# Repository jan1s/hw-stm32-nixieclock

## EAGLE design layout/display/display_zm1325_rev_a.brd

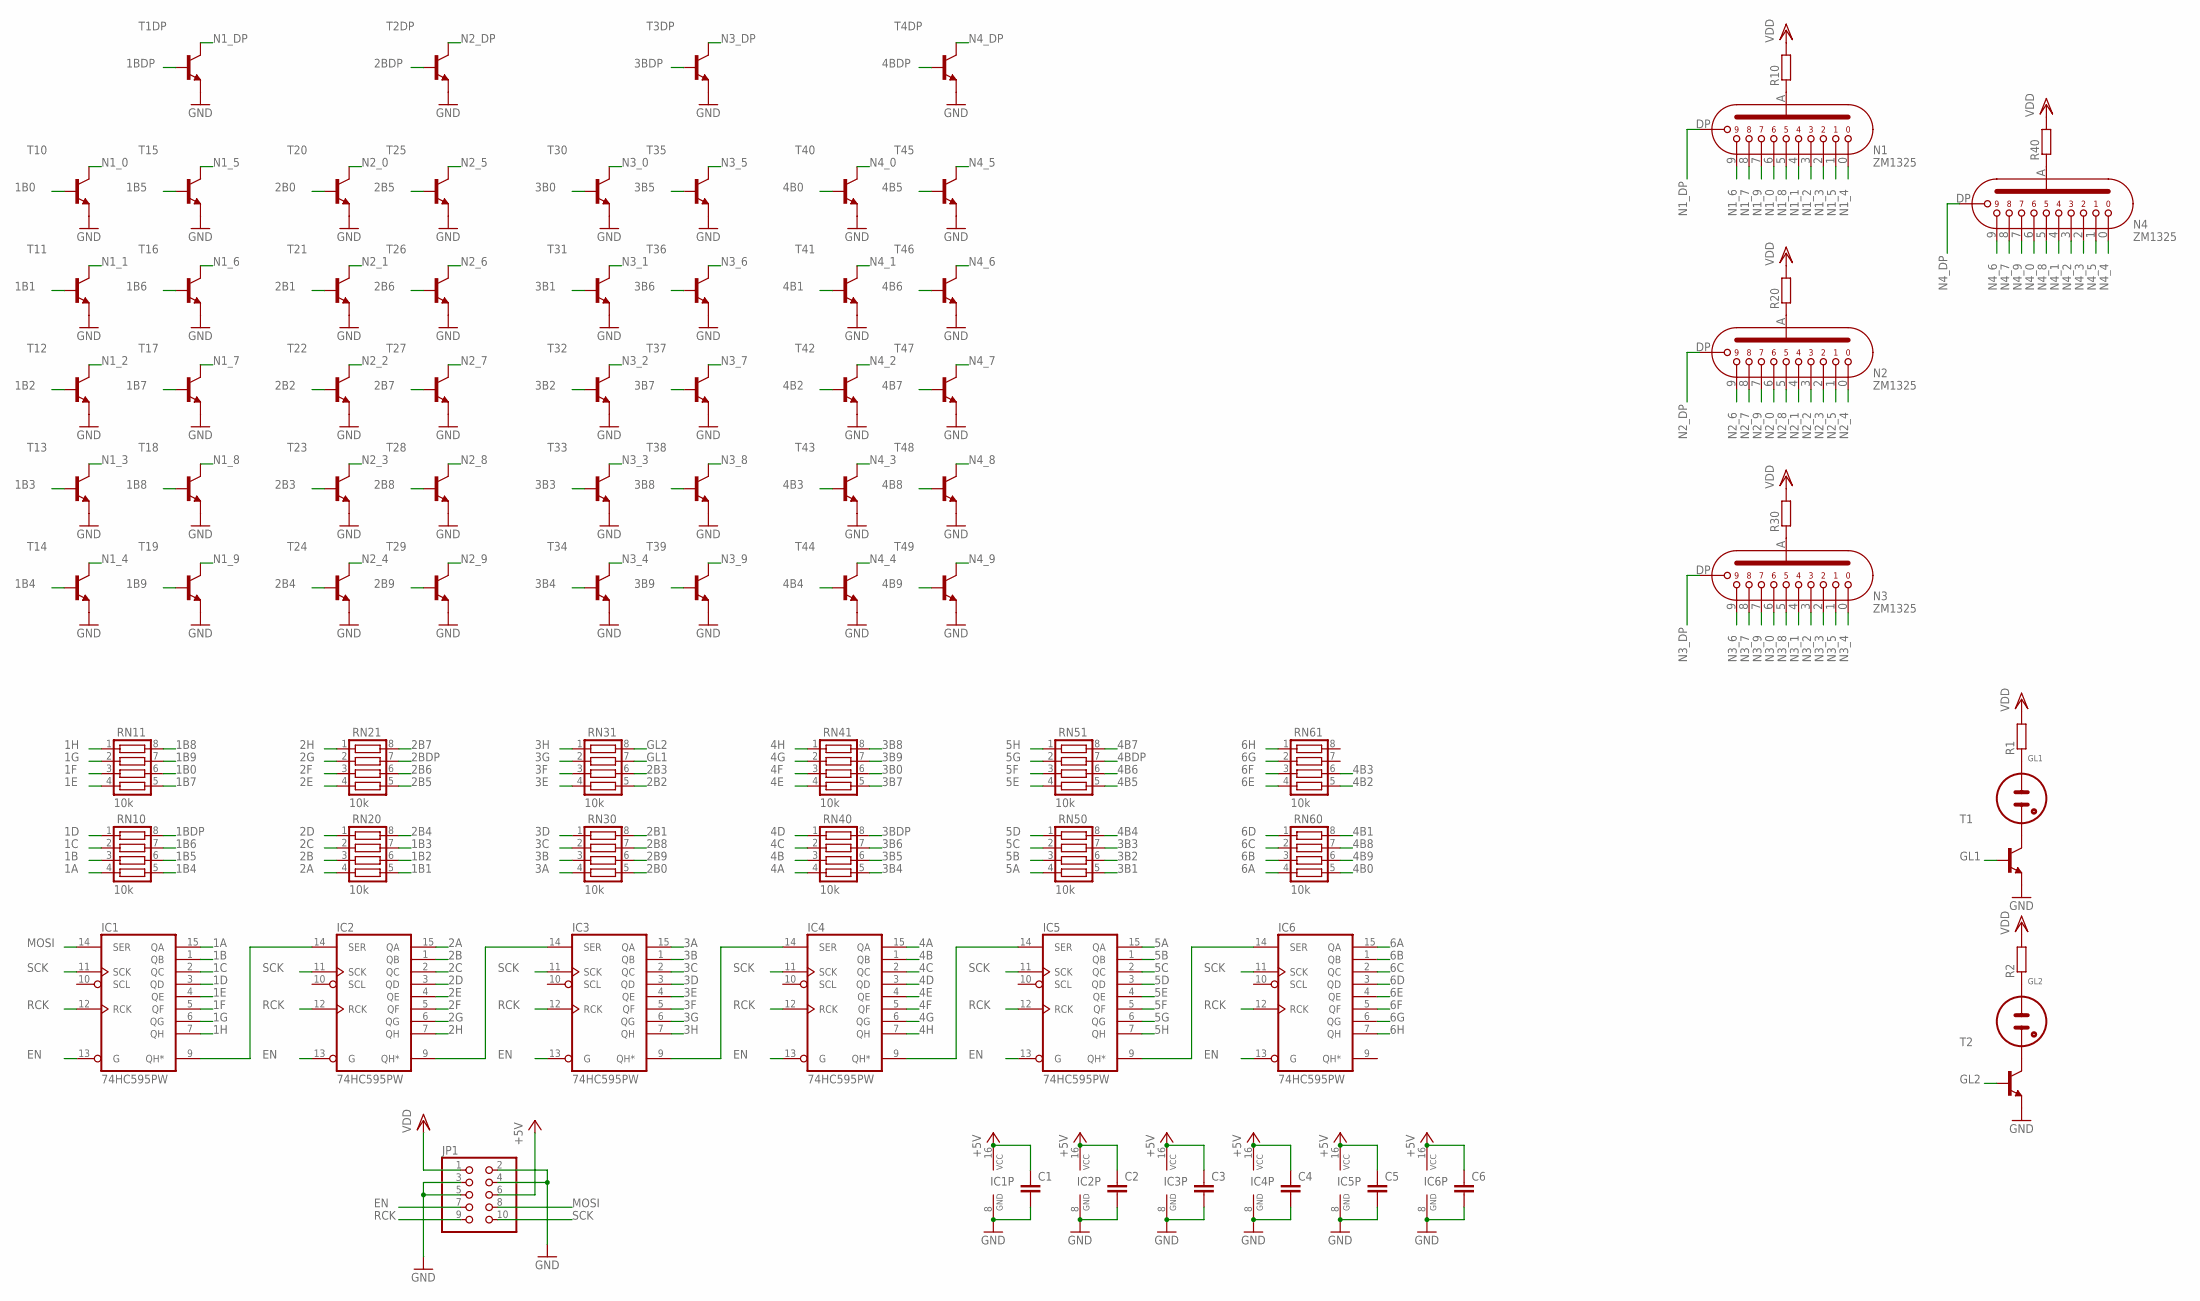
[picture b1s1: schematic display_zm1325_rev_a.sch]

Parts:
C1, C2, C3, C4, C5, C6: C-EUC0603; C0603
GL1, GL2: NE2-NEON-BULB-DRILL
IC1, IC2, IC3, IC4, IC5, IC6: 74HC595PW; TSSOP16
JP1: PINHD-2X5_2.54-SMD; 2X05SMD
N1, N2, N3, N4: ZM1325
R1, R2, R10, R20, R30, R40: R-EU_R0603; R0603
RN10, RN11, RN20, RN21, RN30, RN31, RN40, RN41, RN50, RN51, RN60, RN61: 10k; CTS742C083
T1, T1DP, T2, T2DP, T3DP, T4DP, T10, T11, T12, T13, T14, T15, T16, T17, T18, T19, T20, T21, T22, T23, T24, T25, T26, T27, T28, T29, T30, T31, T32, T33, T34, T35, T36, T37, T38, T39, T40, T41, T42, T43, T44, T45, T46, T47, T48, T49: SMBTA42; SOT23

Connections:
1A: IC1.15 (QA), RN10.4
1B: IC1.1 (QB), RN10.3
1B0: RN11.6, T10.1 (B)
1B1: RN20.5, T11.1 (B)
1B2: RN20.6, T12.1 (B)
1B3: RN20.7, T13.1 (B)
1B4: RN10.5, T14.1 (B)
1B5: RN10.6, T15.1 (B)
1B6: RN10.7, T16.1 (B)
1B7: RN11.5, T17.1 (B)
1B8: RN11.8, T18.1 (B)
1B9: RN11.7, T19.1 (B)
1BDP: RN10.8, T1DP.1 (B)
1C: IC1.2 (QC), RN10.2
1D: IC1.3 (QD), RN10.1
1E: IC1.4 (QE), RN11.4
1F: IC1.5 (QF), RN11.3
1G: IC1.6 (QG), RN11.2
1H: IC1.7 (QH), RN11.1
2A: IC2.15 (QA), RN20.4
2B: IC2.1 (QB), RN20.3
2B0: RN30.5, T20.1 (B)
2B1: RN30.8, T21.1 (B)
2B2: RN31.5, T22.1 (B)
2B3: RN31.6, T23.1 (B)
2B4: RN20.8, T24.1 (B)
2B5: RN21.5, T25.1 (B)
2B6: RN21.6, T26.1 (B)
2B7: RN21.8, T27.1 (B)
2B8: RN30.7, T28.1 (B)
2B9: RN30.6, T29.1 (B)
2BDP: RN21.7, T2DP.1 (B)
2C: IC2.2 (QC), RN20.2
2D: IC2.3 (QD), RN20.1
2E: IC2.4 (QE), RN21.4
2F: IC2.5 (QF), RN21.3
2G: IC2.6 (QG), RN21.2
2H: IC2.7 (QH), RN21.1
3A: IC3.15 (QA), RN30.4
3B: IC3.1 (QB), RN30.3
3B0: RN41.6, T30.1 (B)
3B1: RN50.5, T31.1 (B)
3B2: RN50.6, T32.1 (B)
3B3: RN50.7, T33.1 (B)
3B4: RN40.5, T34.1 (B)
3B5: RN40.6, T35.1 (B)
3B6: RN40.7, T36.1 (B)
3B7: RN41.5, T37.1 (B)
3B8: RN41.8, T38.1 (B)
3B9: RN41.7, T39.1 (B)
3BDP: RN40.8, T3DP.1 (B)
3C: IC3.2 (QC), RN30.2
3D: IC3.3 (QD), RN30.1
3E: IC3.4 (QE), RN31.4
3F: IC3.5 (QF), RN31.3
3G: IC3.6 (QG), RN31.2
3H: IC3.7 (QH), RN31.1
4A: IC4.15 (QA), RN40.4
4B: IC4.1 (QB), RN40.3
4B0: RN60.5, T40.1 (B)
4B1: RN60.8, T41.1 (B)
4B2: RN61.5, T42.1 (B)
4B3: RN61.6, T43.1 (B)
4B4: RN50.8, T44.1 (B)
4B5: RN51.5, T45.1 (B)
4B6: RN51.6, T46.1 (B)
4B7: RN51.8, T47.1 (B)
4B8: RN60.7, T48.1 (B)
4B9: RN60.6, T49.1 (B)
4BDP: RN51.7, T4DP.1 (B)
4C: IC4.2 (QC), RN40.2
4D: IC4.3 (QD), RN40.1
4E: IC4.4 (QE), RN41.4
4F: IC4.5 (QF), RN41.3
4G: IC4.6 (QG), RN41.2
4H: IC4.7 (QH), RN41.1
5A: IC5.15 (QA), RN50.4
5B: IC5.1 (QB), RN50.3
5C: IC5.2 (QC), RN50.2
5D: IC5.3 (QD), RN50.1
5E: IC5.4 (QE), RN51.4
5F: IC5.5 (QF), RN51.3
5G: IC5.6 (QG), RN51.2
5H: IC5.7 (QH), RN51.1
6A: IC6.15 (QA), RN60.4
6B: IC6.1 (QB), RN60.3
6C: IC6.2 (QC), RN60.2
6D: IC6.3 (QD), RN60.1
6E: IC6.4 (QE), RN61.4
6F: IC6.5 (QF), RN61.3
6G: IC6.6 (QG), RN61.2
6H: IC6.7 (QH), RN61.1
+5V: C1.1, C2.1, C3.1, C4.1, C5.1, C6.1, IC1.16 (VCC), IC2.16 (VCC), IC3.16 (VCC), IC4.16 (VCC), IC5.16 (VCC), IC6.16 (VCC), JP1.6
EN: IC1.13 (G), IC2.13 (G), IC3.13 (G), IC4.13 (G), IC5.13 (G), IC6.13 (G), JP1.7
GL1: RN31.7, T1.1 (B)
GL2: RN31.8, T2.1 (B)
GND: C1.2, C2.2, C3.2, C4.2, C5.2, C6.2, IC1.8 (GND), IC2.8 (GND), IC3.8 (GND), IC4.8 (GND), IC5.8 (GND), IC6.8 (GND), JP1.2, JP1.3, JP1.4, JP1.5, T1.2 (E), T1DP.2 (E), T2.2 (E), T2DP.2 (E), T3DP.2 (E), T4DP.2 (E), T10.2 (E), T11.2 (E), T12.2 (E), T13.2 (E), T14.2 (E), T15.2 (E), T16.2 (E), T17.2 (E), T18.2 (E), T19.2 (E), T20.2 (E), T21.2 (E), T22.2 (E), T23.2 (E), T24.2 (E), T25.2 (E), T26.2 (E), T27.2 (E), T28.2 (E), T29.2 (E), T30.2 (E), T31.2 (E), T32.2 (E), T33.2 (E), T34.2 (E), T35.2 (E), T36.2 (E), T37.2 (E), T38.2 (E), T39.2 (E), T40.2 (E), T41.2 (E), T42.2 (E), T43.2 (E), T44.2 (E), T45.2 (E), T46.2 (E), T47.2 (E), T48.2 (E), T49.2 (E)
MOSI: IC1.14 (SER), JP1.8
N1_0: N1.K6 (6), T10.3 (C)
N1_1: N1.K4 (4), T11.3 (C)
N1_2: N1.K3 (3), T12.3 (C)
N1_3: N1.K2 (2), T13.3 (C)
N1_4: N1.K0 (0), T14.3 (C)
N1_5: N1.K1 (1), T15.3 (C)
N1_6: N1.K9 (9), T16.3 (C)
N1_7: N1.K8 (8), T17.3 (C)
N1_8: N1.K5 (5), T18.3 (C)
N1_9: N1.K7 (7), T19.3 (C)
N1_DP: N1.KDP (DP), T1DP.3 (C)
N2_0: N2.K6 (6), T20.3 (C)
N2_1: N2.K4 (4), T21.3 (C)
N2_2: N2.K3 (3), T22.3 (C)
N2_3: N2.K2 (2), T23.3 (C)
N2_4: N2.K0 (0), T24.3 (C)
N2_5: N2.K1 (1), T25.3 (C)
N2_6: N2.K9 (9), T26.3 (C)
N2_7: N2.K8 (8), T27.3 (C)
N2_8: N2.K5 (5), T28.3 (C)
N2_9: N2.K7 (7), T29.3 (C)
N2_DP: N2.KDP (DP), T2DP.3 (C)
N3_0: N3.K6 (6), T30.3 (C)
N3_1: N3.K4 (4), T31.3 (C)
N3_2: N3.K3 (3), T32.3 (C)
N3_3: N3.K2 (2), T33.3 (C)
N3_4: N3.K0 (0), T34.3 (C)
N3_5: N3.K1 (1), T35.3 (C)
N3_6: N3.K9 (9), T36.3 (C)
N3_7: N3.K8 (8), T37.3 (C)
N3_8: N3.K5 (5), T38.3 (C)
N3_9: N3.K7 (7), T39.3 (C)
N3_DP: N3.KDP (DP), T3DP.3 (C)
N4_0: N4.K6 (6), T40.3 (C)
N4_1: N4.K4 (4), T41.3 (C)
N4_2: N4.K3 (3), T42.3 (C)
N4_3: N4.K2 (2), T43.3 (C)
N4_4: N4.K0 (0), T44.3 (C)
N4_5: N4.K1 (1), T45.3 (C)
N4_6: N4.K9 (9), T46.3 (C)
N4_7: N4.K8 (8), T47.3 (C)
N4_8: N4.K5 (5), T48.3 (C)
N4_9: N4.K7 (7), T49.3 (C)
N4_DP: N4.KDP (DP), T4DP.3 (C)
unnamed: GL2.1 (A), R2.1
unnamed: N1.A, R10.1
unnamed: N2.A, R20.1
unnamed: N3.A, R30.1
unnamed: GL2.2 (A1), T2.3 (C)
unnamed: GL1.2 (A1), T1.3 (C)
unnamed: N4.A, R40.1
unnamed: IC1.9 (QH*), IC2.14 (SER)
unnamed: IC2.9 (QH*), IC3.14 (SER)
unnamed: IC3.9 (QH*), IC4.14 (SER)
unnamed: IC4.9 (QH*), IC5.14 (SER)
unnamed: IC5.9 (QH*), IC6.14 (SER)
unnamed: GL1.1 (A), R1.1
RCK: IC1.12 (RCK), IC2.12 (RCK), IC3.12 (RCK), IC4.12 (RCK), IC5.12 (RCK), IC6.12 (RCK), JP1.9
SCK: IC1.11 (SCK), IC2.11 (SCK), IC3.11 (SCK), IC4.11 (SCK), IC5.11 (SCK), IC6.11 (SCK), JP1.10
VDD: JP1.1, R1.2, R2.2, R10.2, R20.2, R30.2, R40.2

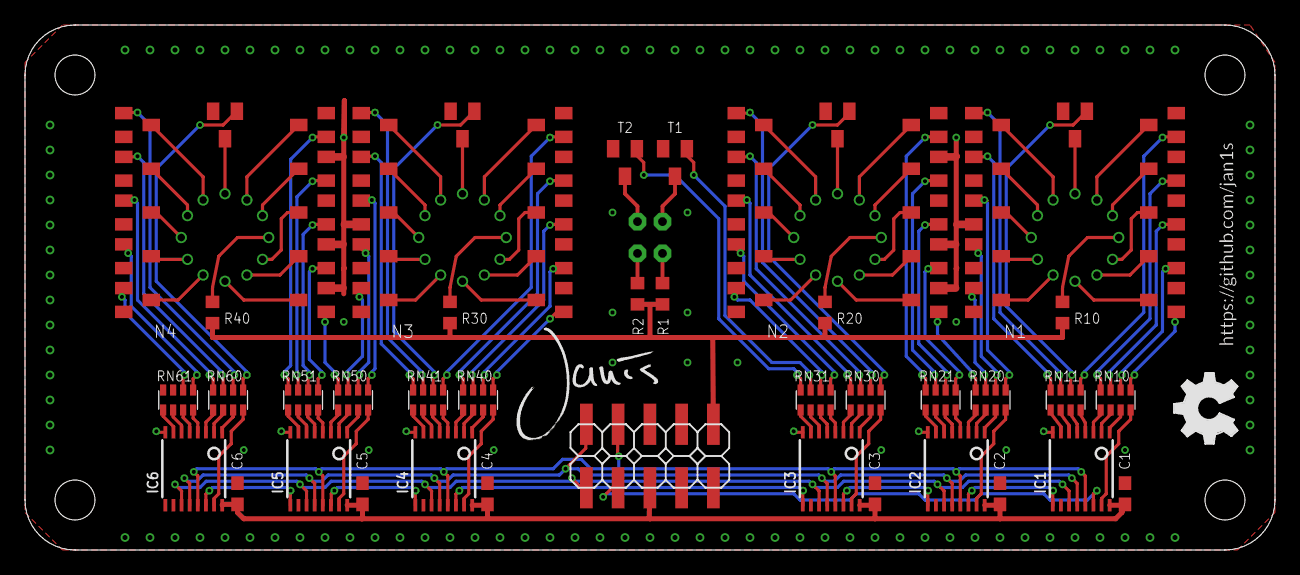
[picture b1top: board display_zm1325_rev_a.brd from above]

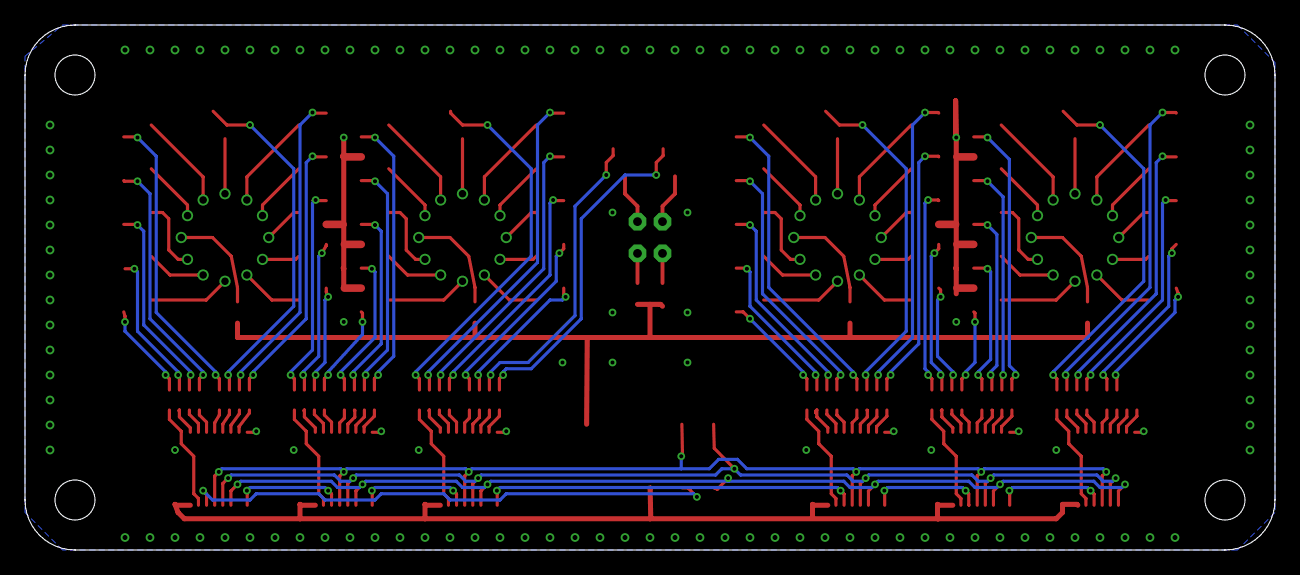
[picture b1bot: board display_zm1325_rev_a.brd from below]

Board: 2 copper layers, 100.0 x 42.0 mm, 86 parts (2 on the bottom side), 158 nets.

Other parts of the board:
U$1: GITHUB/JAN1S
U$2: JANIS_10MM
U$3: OSHW_FILLX200_NOTEXT

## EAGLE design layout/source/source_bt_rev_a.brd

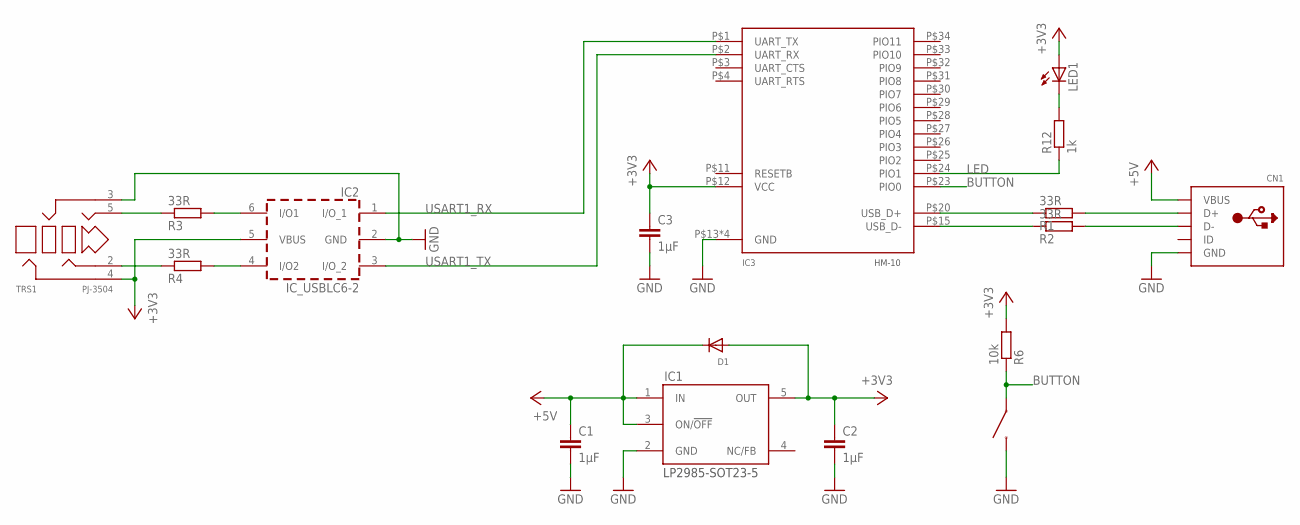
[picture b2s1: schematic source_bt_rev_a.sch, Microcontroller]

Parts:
C1, C2, C3: 1µF; C0603
CN1: USBMINIB; USB-MINIB
D1: DIODESOD-323; SOD-323
IC1: LP2985-SOT23-5; SOT23-5
IC2: IC_USBLC6-2; SOT-23-6L
IC3: HM-10
ISP: TACT-SWITCH-40-40; 40-40
LED1: LEDCHIP-LED0603; CHIP-LED0603
R1, R2, R3, R4: 33R; R0603
R6: 10k; R0603
R12: 1k; R0603
TRS1: PJ-3504; YD-PJ-3504

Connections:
+3V3: C2.1, C3.1, D1.A, IC1.5 (OUT), IC2.5 (VBUS), IC3.P$12 (VCC), LED1.A, R6.2, TRS1.4
+5V: C1.1, CN1.VBUS, D1.C, IC1.1 (IN), IC1.3 (ON/!OFF)
BUTTON: IC3.P$23 (PIO0), ISP.3, ISP.4, R6.1
GND: C1.2, C2.2, C3.2, CN1.GND, IC1.2 (GND), IC2.2 (GND), IC3.P$13 (GND), IC3.P$14 (GND), IC3.P$21 (GND), IC3.P$22 (GND), ISP.1, ISP.2, TRS1.3
LED: IC3.P$24 (PIO1), R12.1
unnamed: IC3.P$20 (USB_D+), R1.1
unnamed: IC3.P$15 (USB_D-), R2.1
unnamed: CN1.D+, R1.2
unnamed: CN1.D-, R2.2
unnamed: IC2.6 (I/O1), R3.2
unnamed: LED1.C, R12.2
unnamed: R4.1, TRS1.2
unnamed: IC2.4 (I/O2), R4.2
unnamed: R3.1, TRS1.5
USART1_RX: IC2.1 (I/O_1), IC3.P$1 (UART_TX)
USART1_TX: IC2.3 (I/O_2), IC3.P$2 (UART_RX)

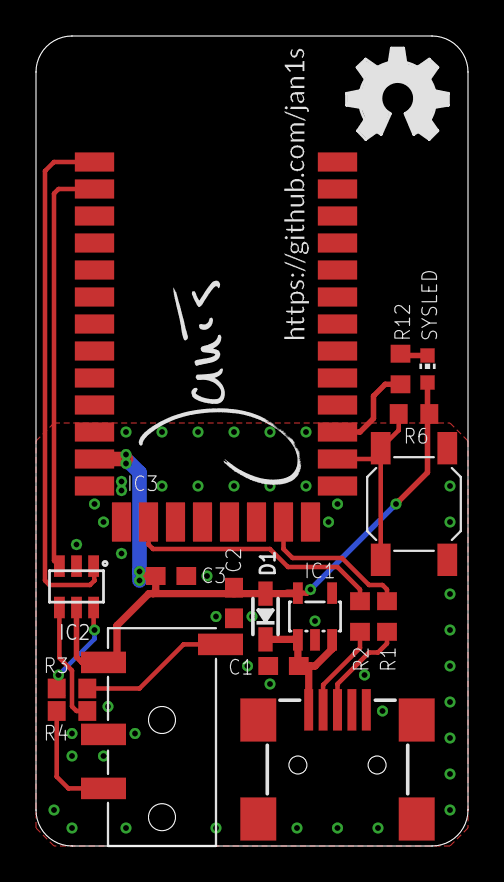
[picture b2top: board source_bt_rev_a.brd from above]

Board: 2 copper layers, 24.0 x 45.0 mm, 22 parts (2 on the bottom side), 16 nets.

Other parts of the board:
LOGO1: OSHW_LOGO_FILLX0200-NT; OSHW_FILLX200_NOTEXT
U$1, U$2: JANIS_10MM
U$5, U$6: GITHUB/JAN1S

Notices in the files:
parts and their libraries:
microbuilder: This work is placed in the public domain, and may be freely used for commercial and non-commercial work with the following conditions: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
